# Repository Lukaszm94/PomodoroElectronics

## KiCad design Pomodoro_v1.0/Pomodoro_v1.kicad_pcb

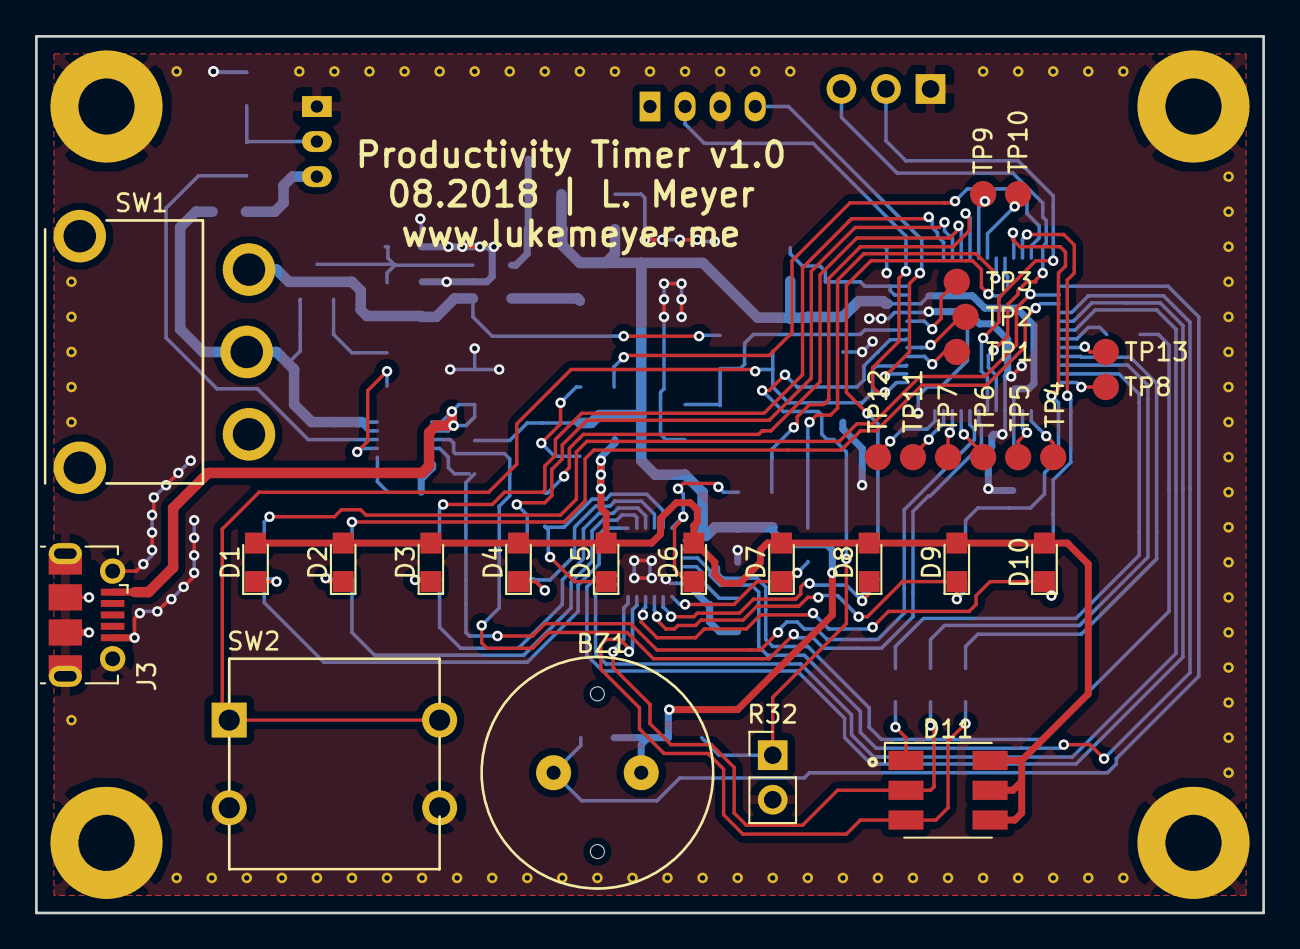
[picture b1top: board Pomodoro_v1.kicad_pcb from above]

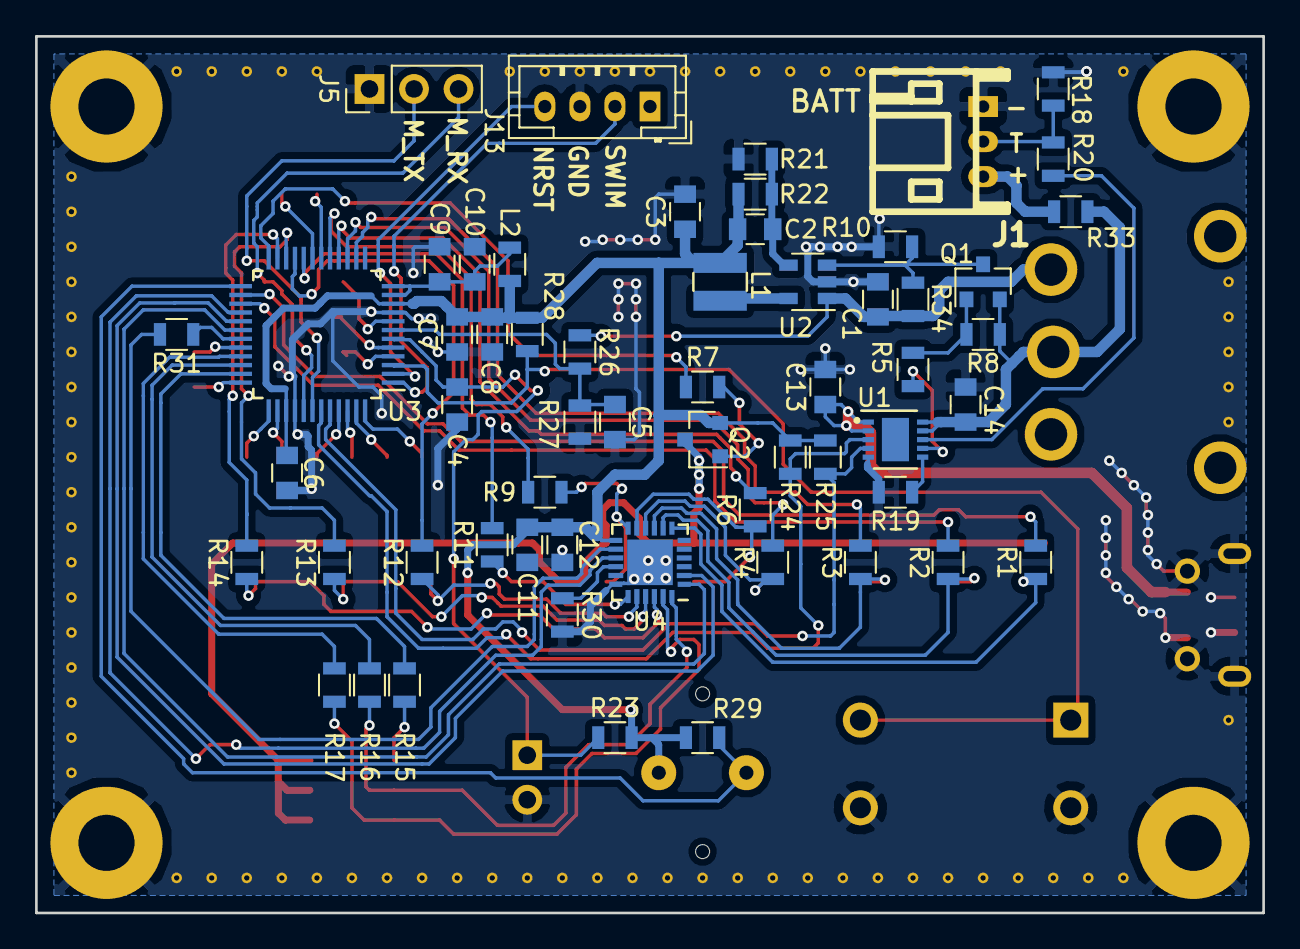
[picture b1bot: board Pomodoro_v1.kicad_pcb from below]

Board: 2 copper layers, 70.0 x 50.0 mm, 91 parts (58 on the bottom side), 72 nets.

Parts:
BZ1: Buzzer; BUZZERS_TDK
C1: 4u7; C_0805
C2: 22p; C_0805
C3, C11, C13, C14: 10u; C_0805
C4, C5, C6, C7, C9, C12: 100n; C_0805
C8, C10: 1u; C_0805
D1, D2: R; LED_0805
D3, D4, D5, D6: Y; LED_0805
D7, D8, D9, D10: G; LED_0805
D11: LED_BGR; LED_RGB_5050-6
J1: BATT; s3b-ph-kl
J3: USB_OTG; USB_Micro-B_Molex-105017-0001
J5: UART; Pin_Header_Straight_1x03_Pitch2.54mm
J13: SWIM; JST_PH_B4B-PH-K_04x2.00mm_Straight
L1: 2u2; LPS3015
L2: BEAD; L_0805
M1, M2, M3, M4: MOUNTING-HOLE; MountingHole_3.2mm_M3_Pad
Q1, Q2: BC807; SOT-23
R1, R2, R3, R4, R6, R9, R17: 200R; R_0805
R5, R10, R22: 100K; R_0805
R7, R26, R34: 10K; R_0805
R8: 1M; R_0805
R11, R12, R13, R14: 10R; R_0805
R15, R16, R31, R33: 0R; R_0805
R18: 66k5; R_0805
R19: 2K49; R_0805
R20: 1k6; R_0805
R21: 390K; R_0805
R23: R; R_0805
R24, R25: 470K; R_0805
R27: 16K2; R_0805
R28: 1M(DNP); R_0805
R29: 1K; R_0805
R30: 4K7; R_0805
R32: R_PHOTO; Pin_Header_Straight_1x02_Pitch2.54mm
SW1: SLIDER; 5MS1S102AM6QE
SW2: BUTTON_SPST; NINIGI_TACTS-24N-F
TP1: PA3; Measurement_Point_Round-SMD-Pad_Small
TP2: PA4; Measurement_Point_Round-SMD-Pad_Small
TP3: PA7; Measurement_Point_Round-SMD-Pad_Small
TP4: PC0; Measurement_Point_Round-SMD-Pad_Small
TP5: PC1; Measurement_Point_Round-SMD-Pad_Small
TP6: PC6; Measurement_Point_Round-SMD-Pad_Small
TP7: PC7; Measurement_Point_Round-SMD-Pad_Small
TP8: PD7; Measurement_Point_Round-SMD-Pad_Small
TP9: PE4; Measurement_Point_Round-SMD-Pad_Small
TP10: PE5; Measurement_Point_Round-SMD-Pad_Small
TP11: PE6; Measurement_Point_Round-SMD-Pad_Small
TP12: PE7; Measurement_Point_Round-SMD-Pad_Small
TP13: PF0; Measurement_Point_Round-SMD-Pad_Small
U1: MCP73833; DFN-10-1EP_3x3mm_Pitch0.5mm
U2: TPS62260; SOT-23-5
U3: STM8L151C2T6; LQFP-48_7x7mm_Pitch0.5mm
U4: AS1122; QFN-24_4x4mm_Pitch0.5mm_NoMask

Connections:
+4V: C1.1, R26.1, R34.1, SW1.3, U2.1
+BATT: C14.1, Q1.2, R8.1, R33.1, SW1.2, U1.9, U1.10
/AS_CLK: U3.29, U4.2
/AS_IRQ: R31.2, U4.14
/AS_SD: U3.30, U4.1
/BAT_V_DIV: C5.1, R26.2, R27.1, U3.7
/BUTTON: R28.2, SW2.1, SW2.2, U3.3
/BUZZER: BZ1.2, R29.2, U3.25
/DO_0: D1.1, R1.1, U4.7
/DO_1: D2.1, R2.1, U4.8
/DO_2: D3.1, R3.1, U4.9
/DO_3: D4.1, R4.1, U4.10
/DO_4: D5.1, R6.1, U4.11
/DO_5: D6.1, R9.1, U4.12
/DO_6: D7.1, R11.1, U4.19
/DO_7: D8.1, R12.1, U4.20
/DO_8: D9.1, R13.1, U4.21
/DO_9: D10.1, R14.1, U4.22
/DO_10: D11.3, R17.1, U4.23
/DO_11: D11.2, R16.1, U4.24
/MCU_UART_RX: J5.3, U3.41
/MCU_UART_TX: J5.2, U3.42
/NRST: J13.4, U3.2
/N_PG: R5.2, U1.7
/PWM_BRIGHTNESS: R7.2, U3.24
/PWM_G1: R11.2, U3.20
/PWM_G2: R12.2, U3.21
/PWM_G3: R13.2, U3.22
/PWM_G4: R14.2, U3.23
/PWM_R1: R1.2, U3.26
/PWM_R2: R2.2, U3.27
/PWM_RGB_B: R15.2, U3.35
/PWM_RGB_G: R16.2, U3.34
/PWM_RGB_R: R17.2, U3.33
/PWM_Y1: R3.2, U3.14
/PWM_Y2: R4.2, U3.15
/PWM_Y3: R6.2, U3.16
/PWM_Y4: R9.2, U3.17
/STAT1: R24.2, U1.3, U3.43
/STAT2: R25.2, U1.4, U3.44
/SWIM: J13.2, U3.1
/THERM: R20.1, U1.8
/V_LDR: C4.1, R23.2, R32.1, U3.6
GND: C1.2, C3.2, C4.2, C5.2, C6.2, C7.2, C8.2, C9.2, C10.2, C11.2, C12.2, C13.2, C14.2, J1.1, J3.5, J3.6, J5.1, J13.3, M1.1, M2.1, M3.1, M4.1, R10.2, R18.2, R19.2, R22.2, R27.2, R30.2, R32.2, SW2.3, SW2.4, U1.5, U2.2, U3.9, U3.40, U4.18, U4.25
unnamed: C2.2, R21.2, R22.1, U2.4
unnamed: C9.1, C10.1, L2.1, U3.11, U3.12
unnamed: D1.2, D2.2, D3.2, D4.2, D5.2, D6.2, D7.2, D8.2, D9.2, D10.2, D11.4, D11.5, D11.6, Q2.3
unnamed: D11.1, R15.1
unnamed: J1.2, R18.1, R20.2
unnamed: J1.3, R33.2
unnamed: L1.1, U2.5
unnamed: Q1.1, R5.1, R8.2
unnamed: Q1.3, R10.1, R34.2, U2.3
unnamed: Q2.1, R7.1
unnamed: R19.1, U1.6
unnamed: R30.1, U4.16
unnamed: R31.1, U3.31
unnamed: TP1.1, U3.4
unnamed: TP2.1, U3.5
unnamed: TP3.1, U3.8
unnamed: TP4.1, U3.37
unnamed: TP5.1, U3.38
unnamed: TP6.1, U3.45
unnamed: TP7.1, U3.46
unnamed: TP8.1, U3.36
unnamed: TP9.1, U3.18
unnamed: TP10.1, U3.19
unnamed: TP11.1, U3.47
unnamed: TP12.1, U3.48
unnamed: TP13.1, U3.32
VBUS: C13.1, J3.1, U1.1, U1.2
VCC: BZ1.1, C2.1, C3.1, C6.1, C7.1, C8.1, C11.1, C12.1, L1.2, L2.2, Q2.2, R21.1, R23.1, R24.1, R25.1, R28.1, R29.1, U3.10, U3.39, U4.13

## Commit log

2018-06-23 gitignore
2018-06-23 Initial electronics commit
2018-06-23 add libraries
2018-06-29 add AS1122 to the schematic, started assigning footprints
2018-07-29 latop update
2018-08-01 assign footprints
2018-08-01 add components: slide switch, buzzer, USB connecotr, tact switch model and son on
2018-08-01 update footprints with 3D models
2018-08-18 remove backup PCB file
2018-08-18 update gitignore
2018-08-18 Add JST connectors library, add STEP files
2018-08-18 Components placement done, initial routing (power tracks)
2018-08-18 fix STAT_x/STATx typo
2018-08-18 routing in progress (mainly CPU section)
2018-08-18 fix D0_x -> DO_x typo
2018-08-18 all signals are routed, need to fix a few GND connections
2018-08-20 finish GND fixes, board is ready for manufacturing
2018-08-20 slightly modify QFN24 package
2018-08-28 add via template for via stitching
2018-08-28 Add via stitching + silkscreen placement
2018-08-28 Generate gerber files
2018-08-28 Minor silkscreen fixes + regenerate gerbers. Board is ready for manufacturing
2018-08-29 add compressed gerber files
2018-08-29 updated BOM
2018-08-29 remove old files
2018-08-29 add missing compononets to BOM
2018-08-29 update BOM with links
2018-09-03 regenerate 3D model
2018-09-03 change JST PH connector 3D model
2018-10-27 add exported PDF schematic
